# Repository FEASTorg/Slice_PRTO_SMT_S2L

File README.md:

# Prototyping Slice

SMT components.

BREAD slice for creating new BREAD slices.

## Introduction

[Short introduction on the project.]

## Usage

[Explain how to use the project. Include examples and screenshots if applicable.]

## Documentation

Please refer to the [docs](/docs) for more info.

---

<div align="center">
  
</div>

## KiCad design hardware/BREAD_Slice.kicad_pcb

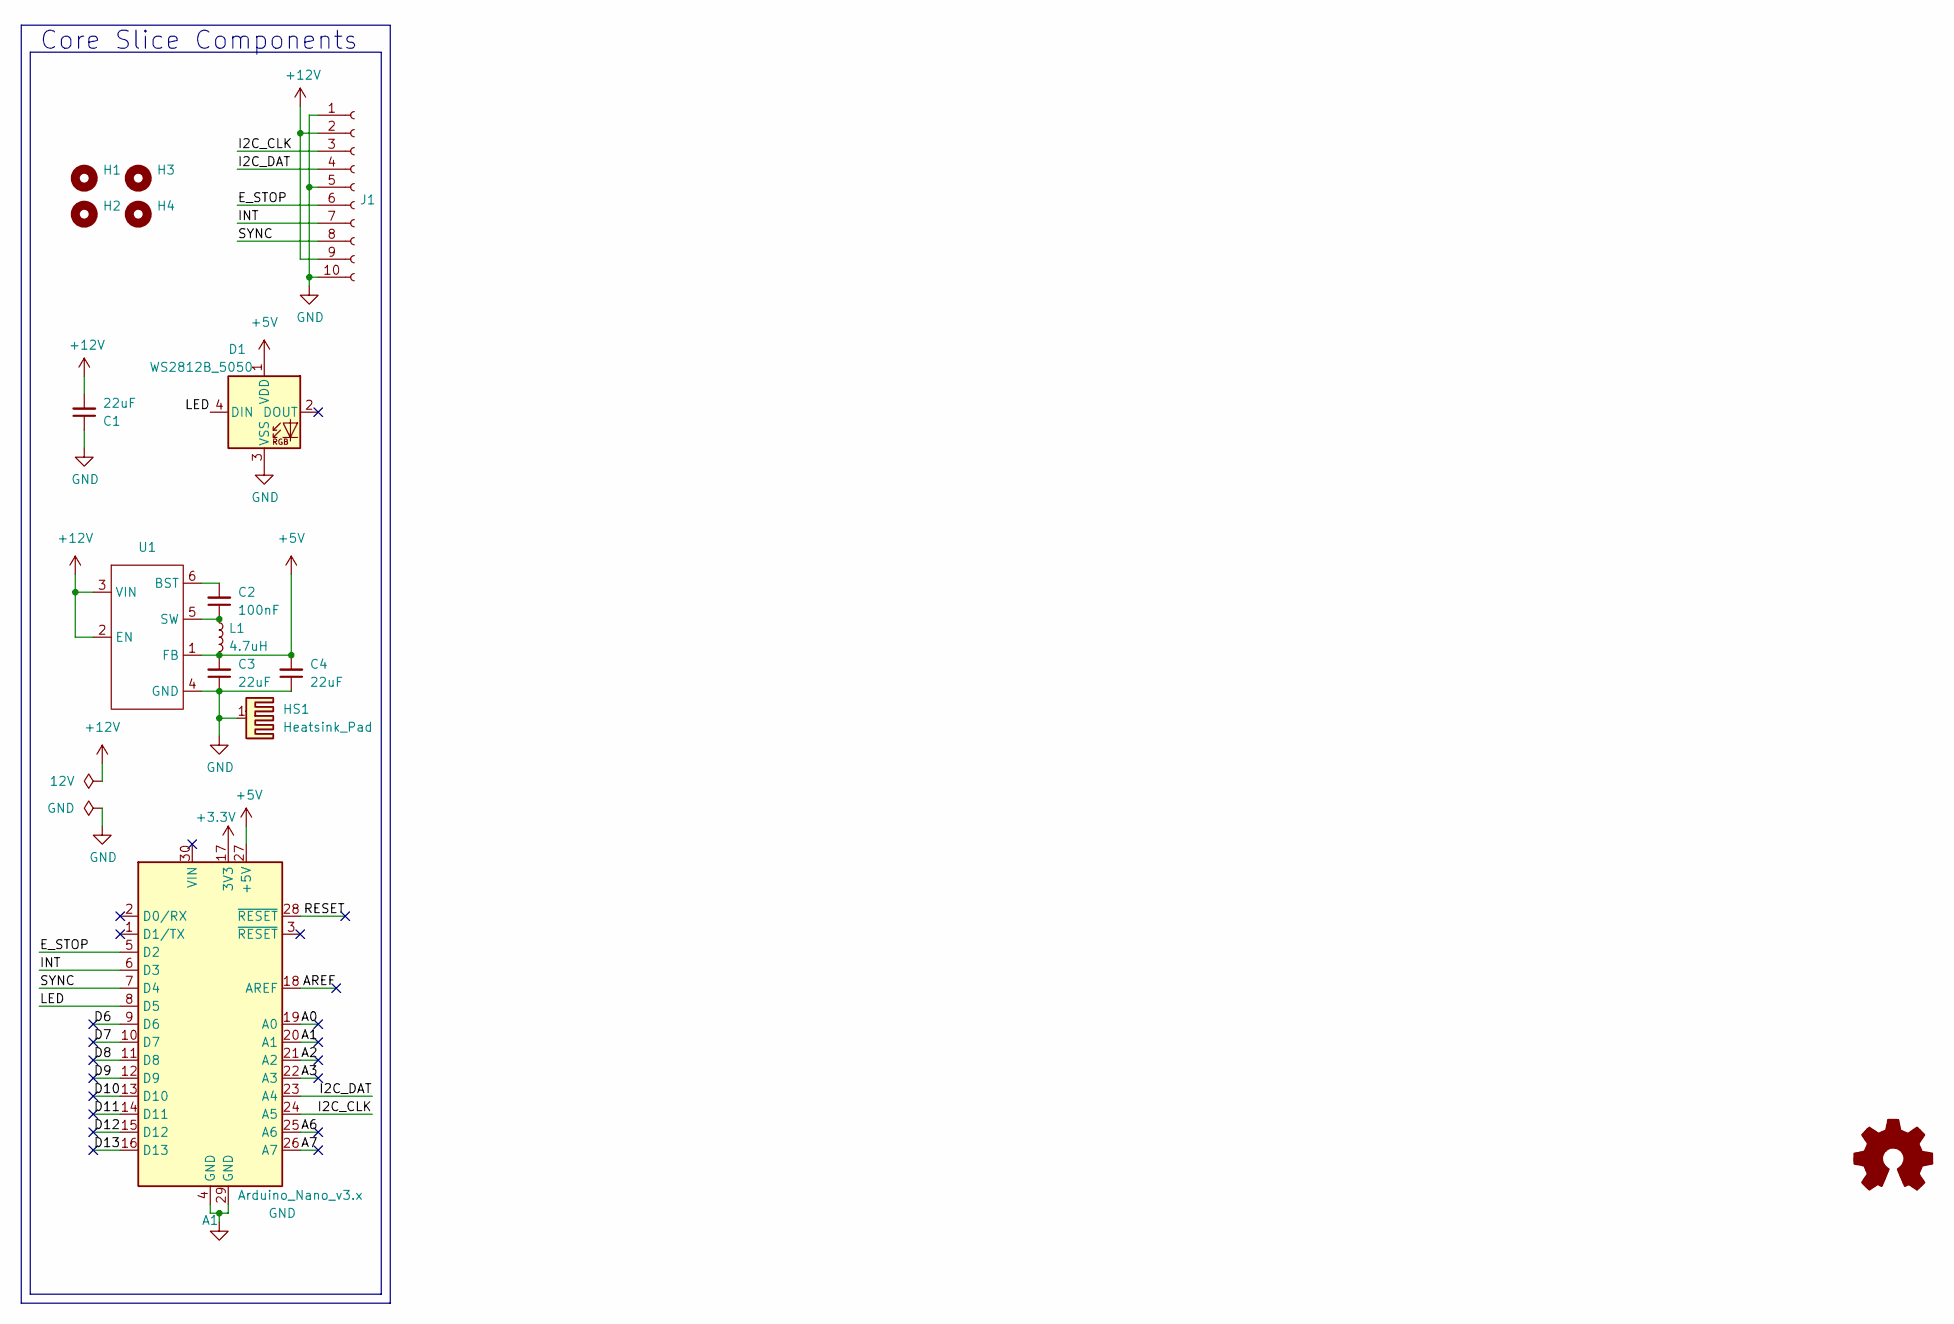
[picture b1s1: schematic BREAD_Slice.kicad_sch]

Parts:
A1: Arduino_Nano_v3.x; Arduino_Nano
C1, C3, C4: 22uF; C_1206_3216Metric
C2: 100nF; C_1206_3216Metric
D1: WS2812B_5050; WS2812-5050-4PIN
H1, H2, H3, H4: MountingHole; MountingHole_5mm
HS1: Heatsink_Pad; Thermal_Pad
J1: Conn_01x10_Female; PinSocket_1x10_P2.54mm_Horizontal
L1: 4.7uH; L_1210_3225Metric
U1: TSOT-23-6

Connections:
+3.3V: A1.17 (3V3)
+5V: A1.27 (+5V), C3.2, C4.2, D1.1 (VDD), L1.2, U1.1 (FB)
+12V: C1.2, J1.2, J1.9, U1.2 (EN), U1.3 (VIN)
/A0: A1.19 (A0)
/A1: A1.20 (A1)
/A2: A1.21 (A2)
/A3: A1.22 (A3)
/A6: A1.25 (A6)
/A7: A1.26 (A7)
/AREF: A1.18 (AREF)
/D6: A1.9 (D6)
/D7: A1.10 (D7)
/D8: A1.11 (D8)
/D9: A1.12 (D9)
/D10: A1.13 (D10)
/D11: A1.14 (D11)
/D12: A1.15 (D12)
/D13: A1.16 (D13)
/E_STOP: A1.5 (D2), J1.6
/I2C_CLK: A1.24 (A5), J1.3
/I2C_DAT: A1.23 (A4), J1.4
/INT: A1.6 (D3), J1.7
/LED: A1.8 (D5), D1.4 (DIN)
/RESET: A1.28 (~RESET)
/SYNC: A1.7 (D4), J1.8
GND: A1.4 (GND), A1.29 (GND), C1.1, C3.1, C4.1, D1.3 (VSS), HS1.1, J1.1, J1.5, J1.10, U1.4 (GND)
unnamed: C2.2, U1.6 (BST)
unnamed: C2.1, L1.1, U1.5 (SW)

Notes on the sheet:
Core Slice Components

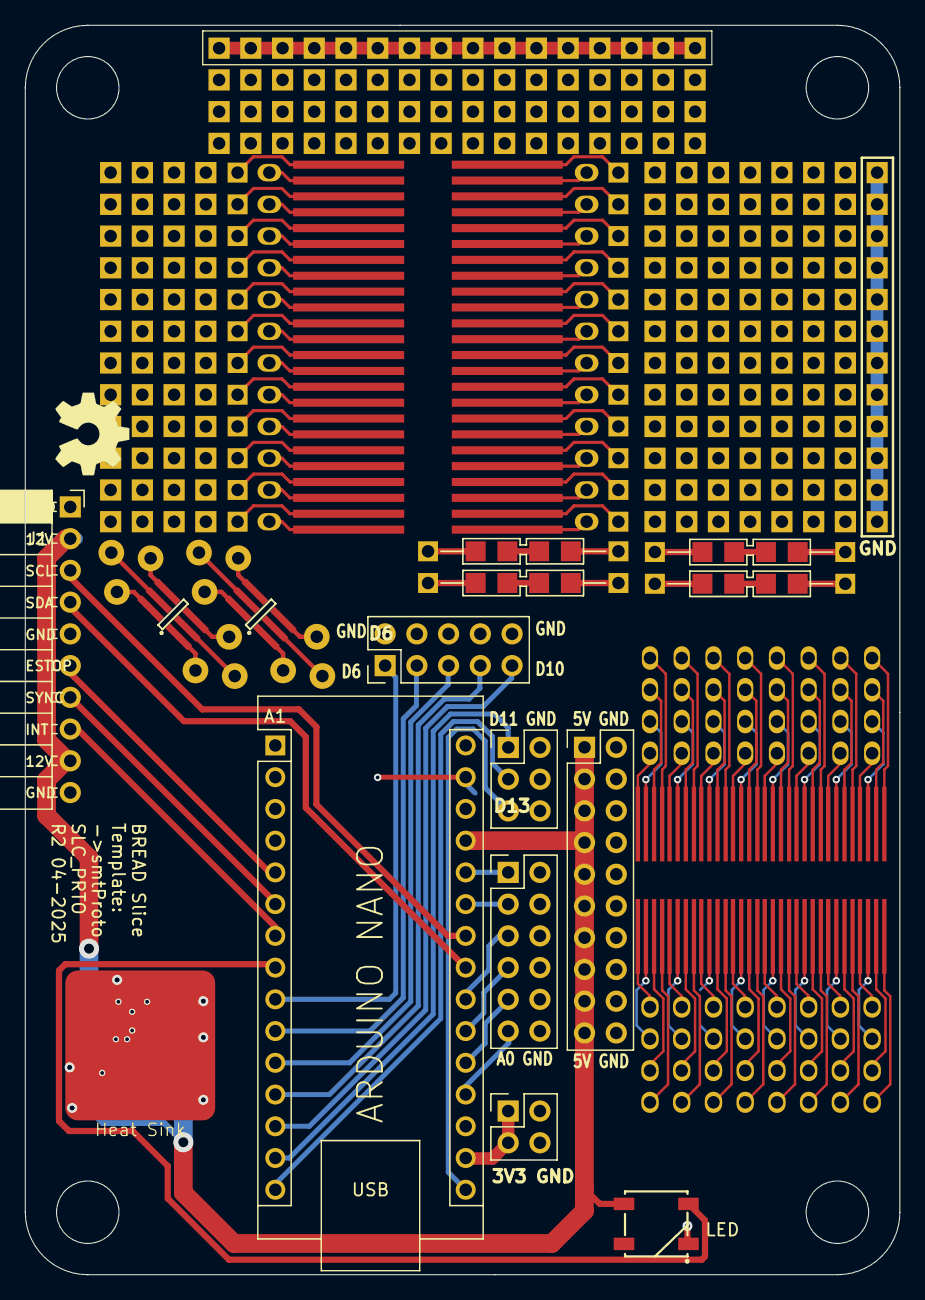
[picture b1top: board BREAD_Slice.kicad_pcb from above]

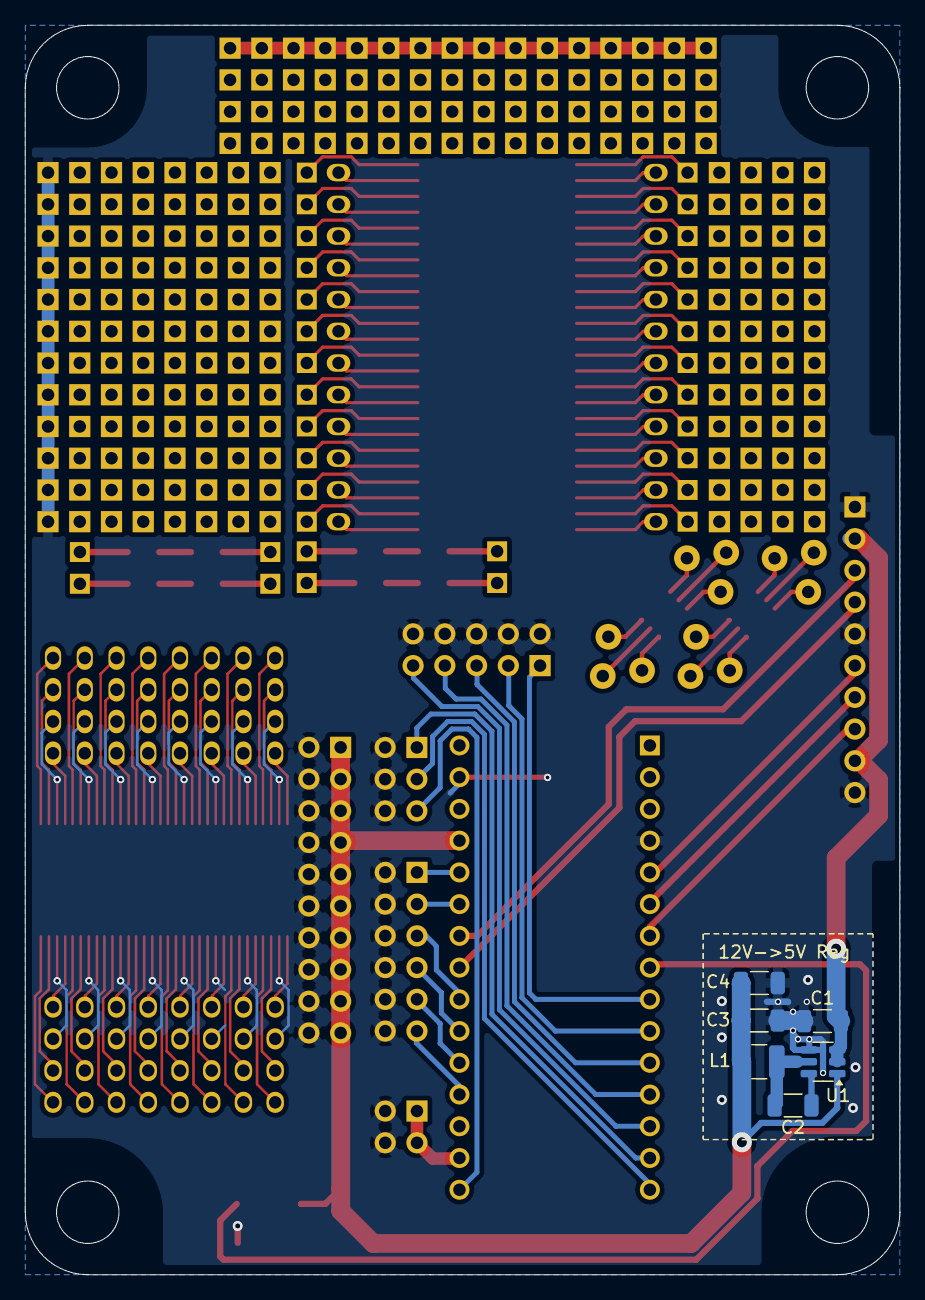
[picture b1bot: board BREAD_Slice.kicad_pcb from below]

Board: 2 copper layers, 70.0 x 100.0 mm, 15 parts (6 on the bottom side), 11 nets.

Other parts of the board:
Logo1: Logo_Open_Hardware_Small; OSHW-Symbol_6.7x6mm_SilkScreen

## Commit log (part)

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2025-09-24 initial commit after split
2025-09-24 ci: initial run of workflow after splitting
2025-09-24 clear erc and drc cheesy way, needs full review like other one to be done proper connected with schem and custom components for proto
2025-09-24 📄 KiBot index + board renders (auto)
2026-01-24 tweak to add more ground pins, need to relocate protolib
2026-01-25 clear backups
2026-01-26 reattach all footprints and revise layout
2026-01-26 remove fw place holder as not relevant
2026-01-26 remove stray readme
2026-01-26 update gitignore
2026-04-20 refactor: org casing rename from 'FEASTorg' to 'feastorg'
2026-05-20 Add slice.yaml manifest (schema v1.0)
2026-05-24 Add standardized TODO.md with Pass 1/Pass 2 structure
